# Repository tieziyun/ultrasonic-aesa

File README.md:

# Ultrasonic AESA panel

A 40 kHz in-air phased array, an acoustic "AESA". It has 64 transducers in an 8 × 8 grid, and each one can transmit or listen under FPGA control, element by element and ping by ping. Eight wideband MEMS microphones sit around the edge of the grid. Every element's raw waveform (amplitude and phase) is digitised and streamed to an ALINX AXU3EGB (Zynq UltraScale+ ZU3EG) board, which does the beamforming.

Uses: 3-D sonar imaging, gesture and hand tracking, Doppler motion sensing, and continuous-wave split mode, where some elements transmit while the rest listen.

**Status (2026-10-24):** the schematic is complete and passes ERC (0 violations). All parts are placed on the 4-layer board (DRC clean, every part with a 3D model); routing is next. Full requirements, decisions and part choices are in [DESIGN_BRIEF.md](DESIGN_BRIEF.md).

## Read the schematic

**[docs/schematics/aesa_schematic.pdf](docs/schematics/aesa_schematic.pdf)**: the whole schematic in one PDF, one A3 page per sheet, regenerated on every schematic change. Page 1 is a block diagram of how the signal flows; click a block to open its sheet, and "<< up to" at the top of each page to go back. The bookmarks follow the hierarchy.

| Page | Sheet | What it is |
|---|---|---|
| 1 | top | **Block diagram**: FPGA → TX drive → transceivers → receive amplifiers → ADCs → FPGA, plus mics and power |
| 2 | `headers` | The two 40-pin ribbon headers to the AXU3EGB, idle pulls and I²C pull-ups |
| 3 | group | The 10 clock buffers and which clock each one feeds |
| 4 | `clk_buf` ×10 | One clock fan-out buffer with 47 Ω series termination |
| 5 | group | TX drive: 16 TX groups and 4 enable buffers |
| 6 | `tx_group` ×16 | 74HCT595 shift register and two UCC27524 gate drivers: drives 4 elements |
| 7 | `en_buf` ×4 | TX-enable buffer for 8 gate drivers |
| 8 | group | The 64 transceiver channels as an 8 × 8 grid |
| 9 | `channel` ×64 | One transceiver: crossed-diode T/R switch, CUSP-TR80 element, limiter, OPA1678 gain stage, 40 kHz band-pass |
| 10 | group | The 16 ADCs, which channels each one digitises, and their I²C groups |
| 11 | `adc` ×16 | TLV320ADC5140, 4 channels at 192 kSPS, input divider, TDM output to the FPGA |
| 12 | group | The 8 microphones, paired on 4 data lines |
| 13 | `mic` ×8 | SPH0641LU4H-1 PDM microphone |
| 14 | `power` | Power 1: 12 V jack → eFuse → VIN, +5 V buck, VDRV 15 V boost (switchable), +3V3, 3V3_MIC, ground test points |
| 15 | `power_analog` | Power 2 (analog): ±6.5 V → low-noise ±5VA for the receivers, +3V3A for the ADCs; the power tree and a bring-up checklist with the expected voltage at every test point |

Each block that repeats is drawn once and reused, so a change to `channel` applies to all 64 channels. KiCad's own export of every instance (126 pages) is left in `build/aesa_schematic_full.pdf`.

## Key numbers

| | |
|---|---|
| Elements | 64 × Same Sky CUSP-TR80-15-2500-TH (40 kHz transceiver, Ø9.8 mm) + 8 × SPH0641LU4H-1 MEMS mics |
| TX drive | 0–15 V square wave per element, 16 serial data lines at 10 MHz, per-element per-sample control |
| RX chain | Gain ×22 (+27 dB) in the amplifier, ×6.7 (+16.5 dB) to the ADC pin after the input divider; 31–51 kHz pass band; 1 m echo 93 dB above the noise ([simulated](sim/reports/README.md)) |
| ADC | 16 × TI TLV320ADC5140, 24-bit, 192 kSPS per channel, all 64 channels sampled at once, TDM to the FPGA, I²C configuration |
| Power | One 12 V barrel jack (≥ 1.5 A); every rail has a test point, an isolation jumper and (except the analog LDOs) an LED |
| Board | One 4-layer board, 192 × 301 mm (JLC04161H-7628, ENIG): transducers on the front, all SMT parts on the back |
| FPGA link | Two 40-pin ribbons, 3.3 V LVCMOS, about 15 cm |

## Repository

| Path | Contents |
|---|---|
| [DESIGN_BRIEF.md](DESIGN_BRIEF.md) | Requirements, decisions with reasons and sources, parts, pinouts, open questions |
| `kicad/` | KiCad 10 project `aesa.kicad_pro`, the source of truth |
| `scripts/` | Generators: `build_cells.py` (every cell sheet except `channel`: ADC, TX, buffers, mic, headers, power), `gen_top.py` (block diagram, group sheets, references), `sch_annotate.py` (channel title and notes), `export_pdf.py` (PDFs), plus field and LCSC helpers |
| `skidl/` | Reference spec of each block in SKiDL (values, nets, LCSC numbers) |
| `sim/` | LTspice testbenches and models. `sim/run.py` exports the channel circuit from the KiCad schematic, runs every testbench and writes [sim/reports/](sim/reports/README.md) |
| `docs/schematics/` | The schematic PDF (one page per sheet, linked) |
| `docs/assembly/` | Assembly drawing (front and back with every reference), for building and repair |
| `docs/datasheets/` | A datasheet PDF for every part on the board, with an [index](docs/datasheets/README.md); kept in step with the BOM by `scripts/datasheets.py` |
| [CLAUDE.md](CLAUDE.md) | Working rules for the AI assistant on this project |

## Rebuild

Tools: KiCad 10.0 (per-user install) and LTspice 24. Run from the repository root in a Windows terminal:

```
set KPY=%LOCALAPPDATA%\Programs\KiCad\10.0\bin\python.exe
set KCLI=%LOCALAPPDATA%\Programs\KiCad\10.0\bin\kicad-cli.exe
%KPY% scripts\build_cells.py
%KPY% scripts\sch_annotate.py
%KPY% scripts\sch_lcsc.py kicad\adc.kicad_sch kicad\tx_group.kicad_sch kicad\en_buf.kicad_sch kicad\clk_buf.kicad_sch kicad\mic.kicad_sch kicad\headers.kicad_sch kicad\power.kicad_sch kicad\power_analog.kicad_sch
%KPY% scripts\gen_top.py
%KCLI% sch erc kicad\aesa.kicad_sch
%KPY% sim\run.py
```

The `channel` sheet is drawn by hand (with the KiCad MCP server) and is not regenerated; everything else is. `gen_top.py` ends by exporting the schematic PDF, and the git pre-commit hook (`.githooks/pre-commit`, enabled with `git config core.hooksPath .githooks`) refuses a commit that changes a sheet without the matching PDF.

Board (placement, 3D models, assembly drawing):

```
%KPY% scripts\make_3d.py
%KPY% scripts\place.py
%KPY% scripts\placement_check.py
%KCLI% pcb drc kicadesa.kicad_pcb
%KPY% scriptsssembly_pdf.py
```

BOM (needs internet: it queries JLCPCB for parts, stock and prices, and takes a few minutes):

```
%KPY% scripts\bom.py
%KPY% scripts\sch_lcsc.py --force kicad\channel.kicad_sch kicad\adc.kicad_sch kicad\tx_group.kicad_sch kicad\en_buf.kicad_sch kicad\clk_buf.kicad_sch kicad\mic.kicad_sch kicad\headers.kicad_sch kicad\power.kicad_sch kicad\power_analog.kicad_sch
%KPY% scripts\gen_top.py
```

`bom.py` writes the costed BOM `docs/bom.md`, the JLCPCB upload file `fab/bom_jlcpcb.csv` and `scripts/parts.json`, from which `sch_lcsc.py` fills every part's LCSC field.

## Next

1. Routing (power by hand first, then Freerouting), then fabrication outputs for JLCPCB.
2. Waveguide design and FPGA firmware (XDC constraints, ADC register setup, TX bit streaming).

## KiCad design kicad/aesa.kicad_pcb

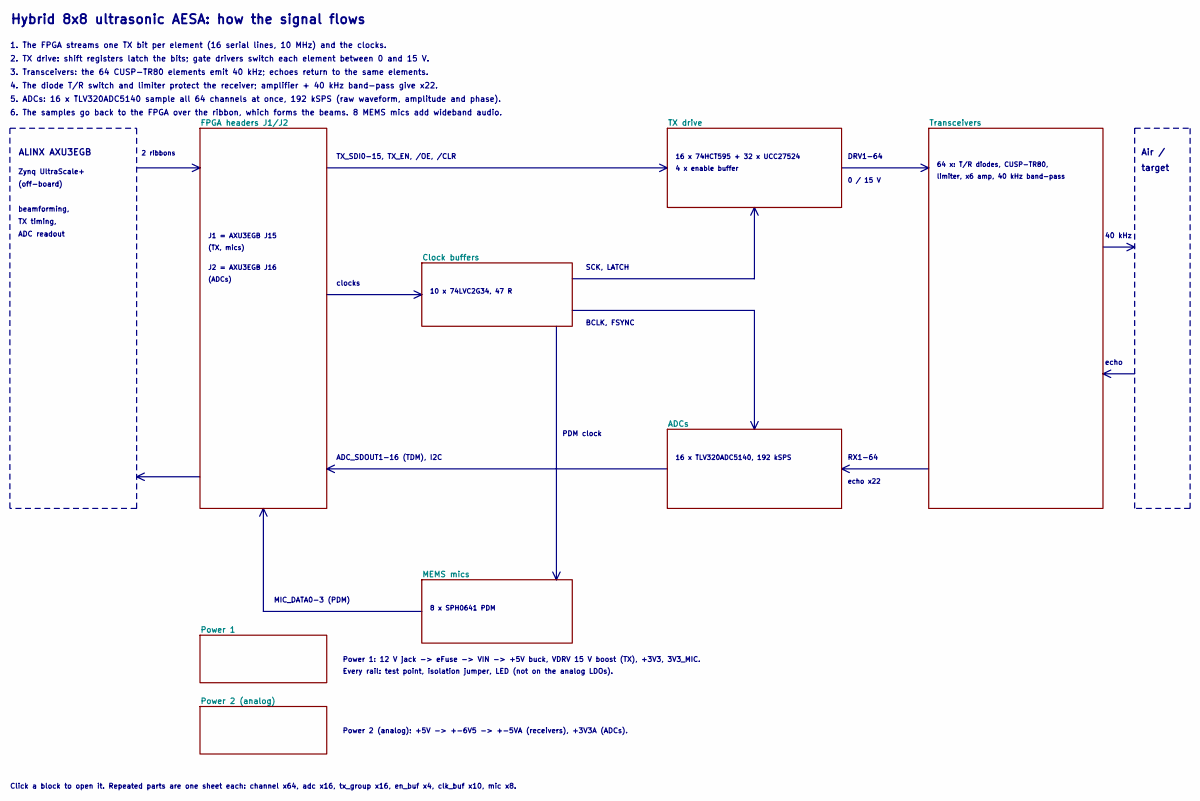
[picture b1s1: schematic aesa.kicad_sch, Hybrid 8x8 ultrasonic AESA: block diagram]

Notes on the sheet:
Hybrid 8x8 ultrasonic AESA: how the signal flows
1. The FPGA streams one TX bit per element (16 serial lines, 10 MHz) and the clocks.
2. TX drive: shift registers latch the bits; gate drivers switch each element between 0 and 15 V.
3. Transceivers: the 64 CUSP-TR80 elements emit 40 kHz; echoes return to the same elements.
4. The diode T/R switch and limiter protect the receiver; amplifier + 40 kHz band-pass give x22.
5. ADCs: 16 x TLV320ADC5140 sample all 64 channels at once, 192 kSPS (raw waveform, amplitude and phase).
6. The samples go back to the FPGA over the ribbon, which forms the beams. 8 MEMS mics add wideband audio.
ALINX AXU3EGB
Zynq UltraScale+
(off-board)
beamforming,
TX timing,
ADC readout
Air /
target
2 ribbons
TX_SDI0-15, TX_EN, /OE, /CLR
clocks
SCK, LATCH
BCLK, FSYNC
PDM clock
DRV1-64
0 / 15 V
40 kHz
echo
RX1-64
echo x22
ADC_SDOUT1-16 (TDM), I2C
MIC_DATA0-3 (PDM)
16 x 74HCT595 + 32 x UCC27524
4 x enable buffer
64 x: T/R diodes, CUSP-TR80,
limiter, x6 amp, 40 kHz band-pass
16 x TLV320ADC5140, 192 kSPS
10 x 74LVC2G34, 47 R
8 x SPH0641 PDM
J1 = AXU3EGB J15
(TX, mics)
J2 = AXU3EGB J16
(ADCs)

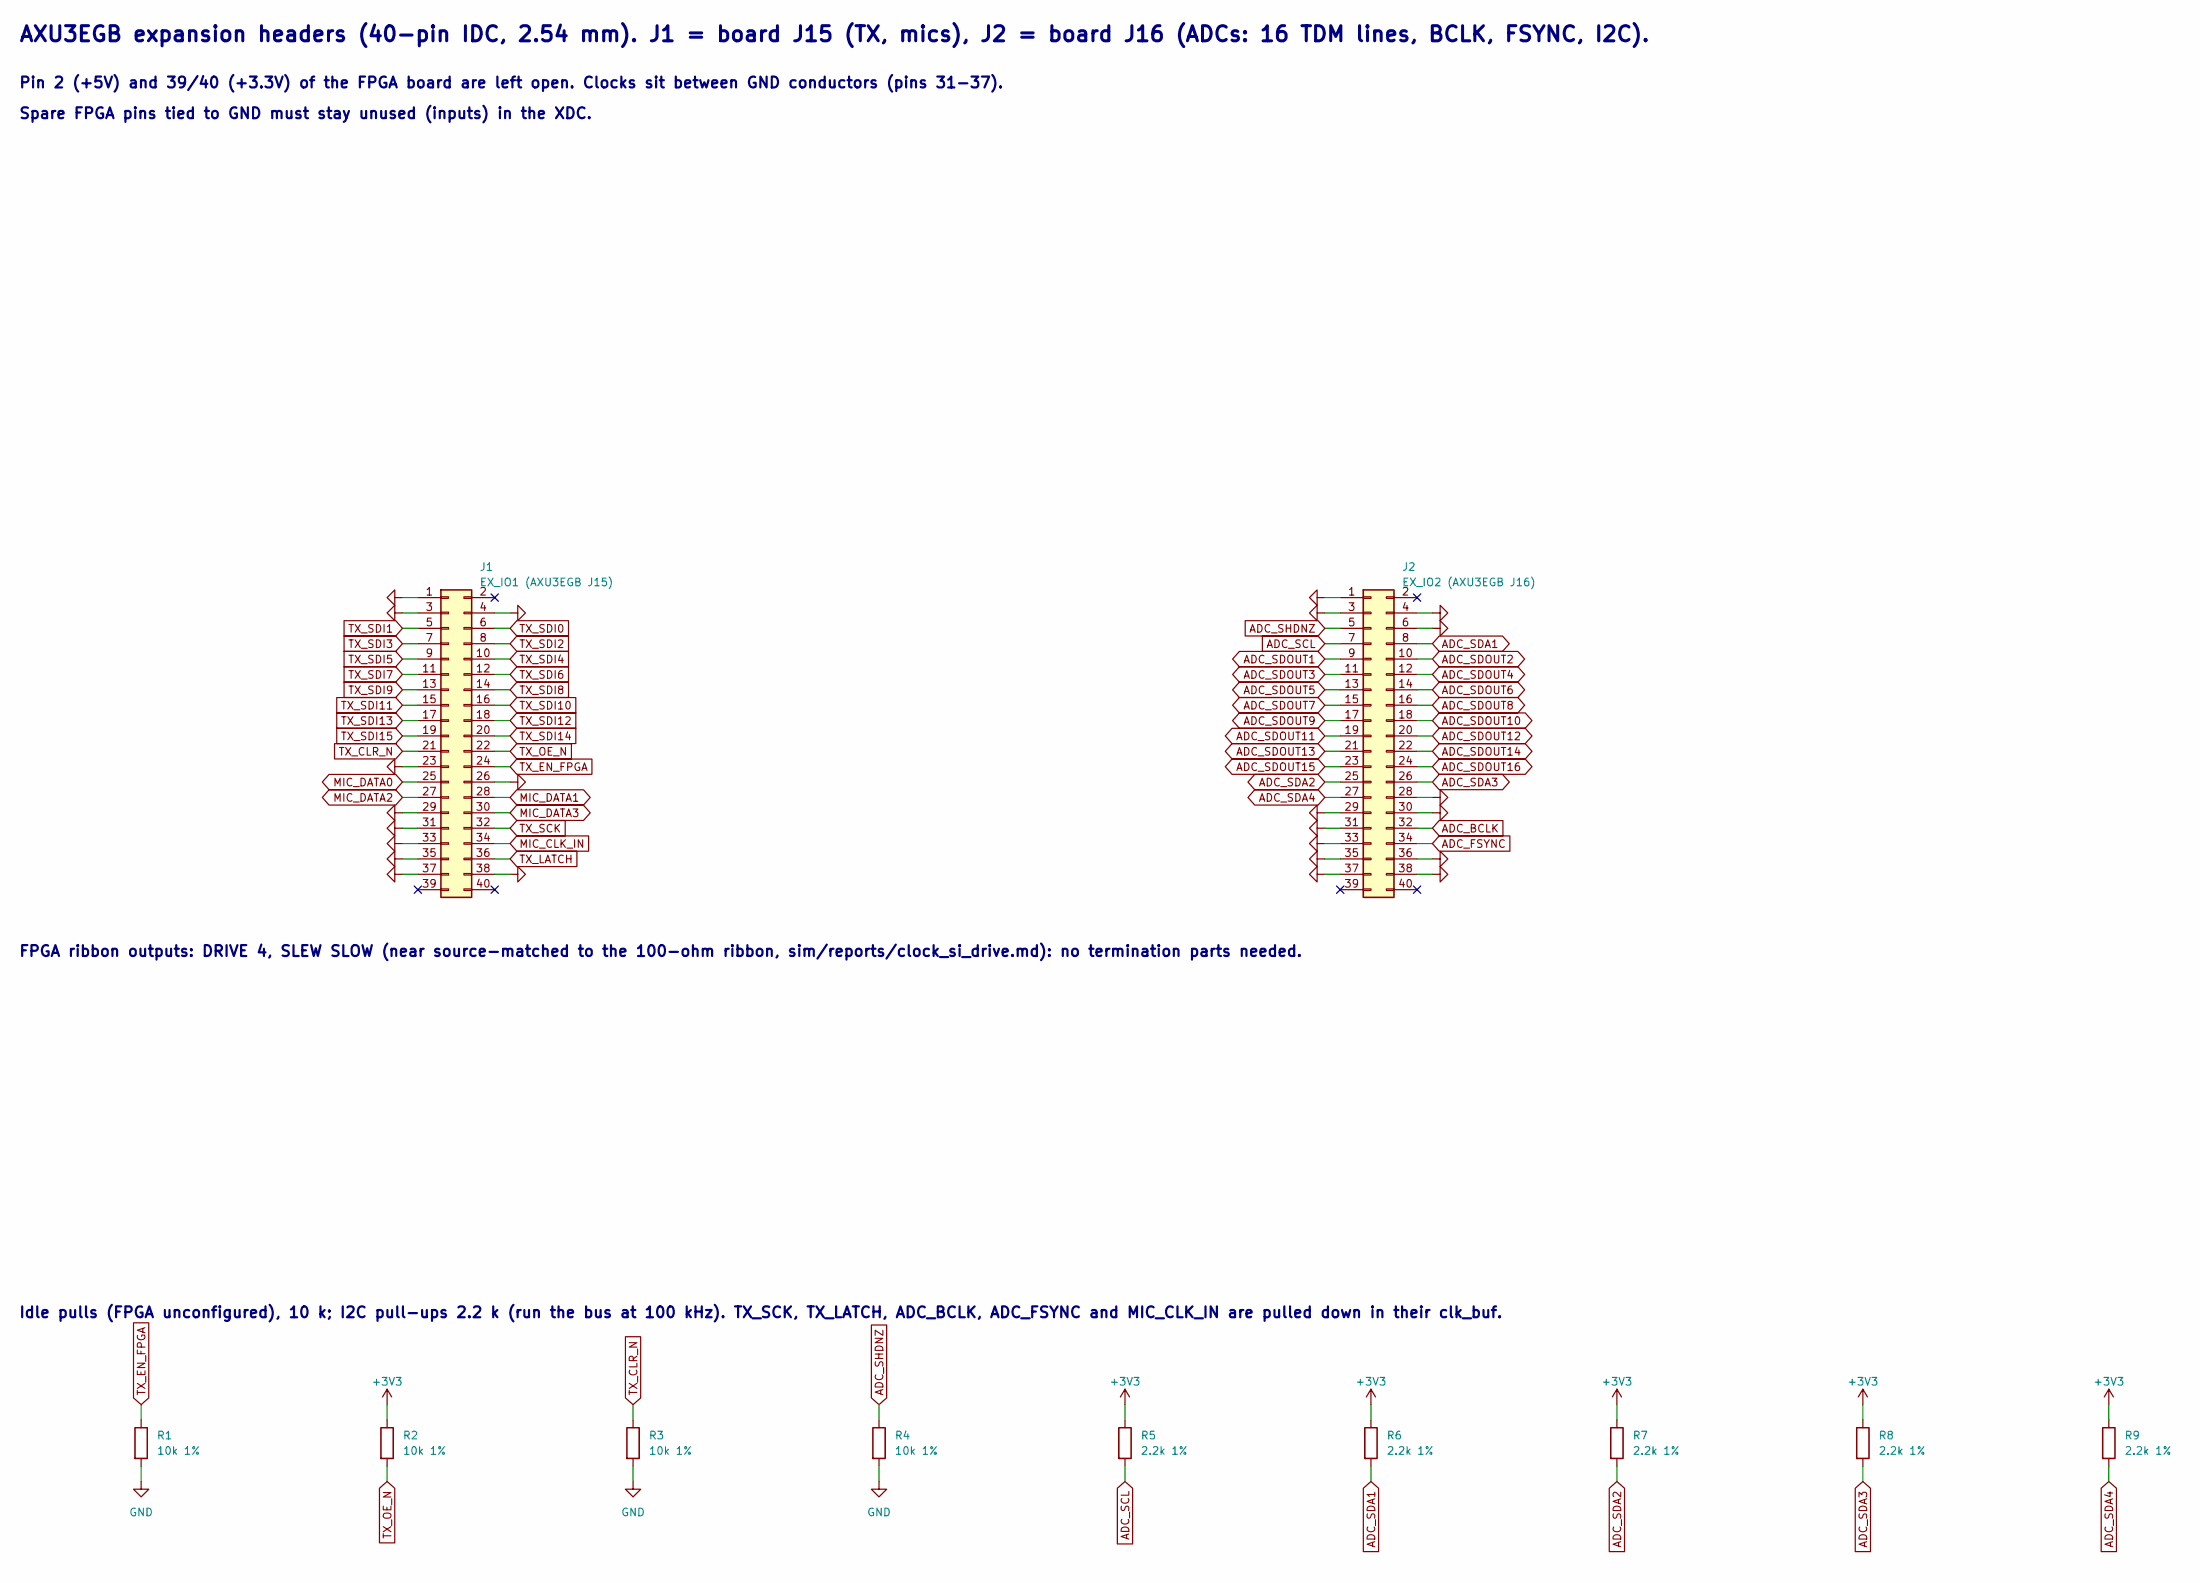
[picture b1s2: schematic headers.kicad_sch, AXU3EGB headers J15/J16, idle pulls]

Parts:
J1: EX_IO1 (AXU3EGB J15); IDC-Header_2x20_P2.54mm_Vertical; LCSC C19193815
J2: EX_IO2 (AXU3EGB J16); IDC-Header_2x20_P2.54mm_Vertical; LCSC C19193815
R1, R2, R3, R4: 10k 1%; R_0603_1608Metric; LCSC C25804
R5, R6, R7, R8, R9: 2.2k 1%; R_0603_1608Metric; LCSC C4190

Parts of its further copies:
J9901: EX_IO1 (AXU3EGB J15); IDC-Header_2x20_P2.54mm_Vertical; LCSC C19193815
J9902: EX_IO2 (AXU3EGB J16); IDC-Header_2x20_P2.54mm_Vertical; LCSC C19193815
R9901, R9902, R9903, R9904: 10k 1%; R_0603_1608Metric; LCSC C25804
R9905, R9906, R9907, R9908, R9909: 2.2k 1%; R_0603_1608Metric; LCSC C4190

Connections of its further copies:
+3V3: R9902.1, R9905.1, R9906.1, R9907.1, R9908.1, R9909.1; also elsewhere on the board
ADC_BCLK: J9902.32; also elsewhere on the board
ADC_FSYNC: J9902.34; also elsewhere on the board
ADC_SCL: J9902.7, R9905.2; also elsewhere on the board
ADC_SDA1: J9902.8, R9906.2; also elsewhere on the board
ADC_SDA2: J9902.25, R9907.2; also elsewhere on the board
ADC_SDA3: J9902.26, R9908.2; also elsewhere on the board
ADC_SDA4: J9902.27, R9909.2; also elsewhere on the board
ADC_SDOUT1: J9902.9; also elsewhere on the board
ADC_SDOUT2: J9902.10; also elsewhere on the board
ADC_SDOUT3: J9902.11; also elsewhere on the board
ADC_SDOUT4: J9902.12; also elsewhere on the board
ADC_SDOUT5: J9902.13; also elsewhere on the board
ADC_SDOUT6: J9902.14; also elsewhere on the board
ADC_SDOUT7: J9902.15; also elsewhere on the board
ADC_SDOUT8: J9902.16; also elsewhere on the board
ADC_SDOUT9: J9902.17; also elsewhere on the board
ADC_SDOUT10: J9902.18; also elsewhere on the board
ADC_SDOUT11: J9902.19; also elsewhere on the board
ADC_SDOUT12: J9902.20; also elsewhere on the board
ADC_SDOUT13: J9902.21; also elsewhere on the board
ADC_SDOUT14: J9902.22; also elsewhere on the board
ADC_SDOUT15: J9902.23; also elsewhere on the board
ADC_SDOUT16: J9902.24; also elsewhere on the board
ADC_SHDNZ: J9902.5, R9904.1; also elsewhere on the board
GND: J9901.1, J9901.3, J9901.4, J9901.23, J9901.26, J9901.29, J9901.31, J9901.33, J9901.35, J9901.37, J9901.38, J9902.1, J9902.3, J9902.4, J9902.6, J9902.28, J9902.29, J9902.30, J9902.31, J9902.33, J9902.35, J9902.36, J9902.37, J9902.38, R9901.2, R9903.2, R9904.2; also elsewhere on the board
MIC_CLK_IN: J9901.34; also elsewhere on the board
MIC_DATA0: J9901.25; also elsewhere on the board
MIC_DATA1: J9901.28; also elsewhere on the board
MIC_DATA2: J9901.27; also elsewhere on the board
MIC_DATA3: J9901.30; also elsewhere on the board
TX_CLR_N: J9901.21, R9903.1; also elsewhere on the board
TX_EN_FPGA: J9901.24, R9901.1; also elsewhere on the board
TX_LATCH: J9901.36; also elsewhere on the board
TX_OE_N: J9901.22, R9902.2; also elsewhere on the board
TX_SCK: J9901.32; also elsewhere on the board
TX_SDI0: J9901.6; also elsewhere on the board
TX_SDI1: J9901.5; also elsewhere on the board
TX_SDI2: J9901.8; also elsewhere on the board
TX_SDI3: J9901.7; also elsewhere on the board
TX_SDI4: J9901.10; also elsewhere on the board
TX_SDI5: J9901.9; also elsewhere on the board
TX_SDI6: J9901.12; also elsewhere on the board
TX_SDI7: J9901.11; also elsewhere on the board
TX_SDI8: J9901.14; also elsewhere on the board
TX_SDI9: J9901.13; also elsewhere on the board
TX_SDI10: J9901.16; also elsewhere on the board
TX_SDI11: J9901.15; also elsewhere on the board
TX_SDI12: J9901.18; also elsewhere on the board
TX_SDI13: J9901.17; also elsewhere on the board
TX_SDI14: J9901.20; also elsewhere on the board
TX_SDI15: J9901.19; also elsewhere on the board

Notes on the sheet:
Idle pulls (FPGA unconfigured), 10 k; I2C pull-ups 2.2 k (run the bus at 100 kHz). TX_SCK, TX_LATCH, ADC_BCLK, ADC_FSYNC and MIC_CLK_IN are pulled down in their clk_buf.
Pin 2 (+5V) and 39/40 (+3.3V) of the FPGA board are left open. Clocks sit between GND conductors (pins 31-37).
Spare FPGA pins tied to GND must stay unused (inputs) in the XDC.
AXU3EGB expansion headers (40-pin IDC, 2.54 mm). J1 = board J15 (TX, mics), J2 = board J16 (ADCs: 16 TDM lines, BCLK, FSYNC, I2C).
FPGA ribbon outputs: DRIVE 4, SLEW SLOW (near source-matched to the 100-ohm ribbon, sim/reports/clock_si_drive.md): no termination parts needed.

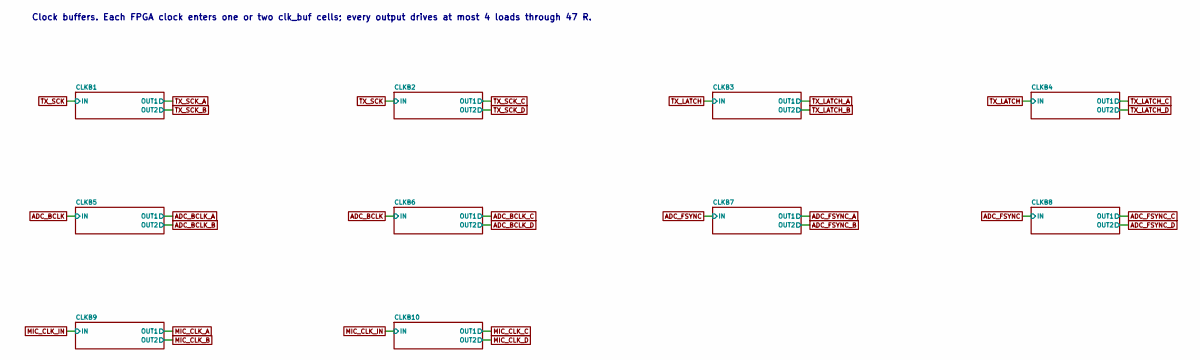
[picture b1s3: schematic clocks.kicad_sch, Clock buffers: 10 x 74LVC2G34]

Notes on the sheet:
Clock buffers. Each FPGA clock enters one or two clk_buf cells; every output drives at most 4 loads through 47 R.

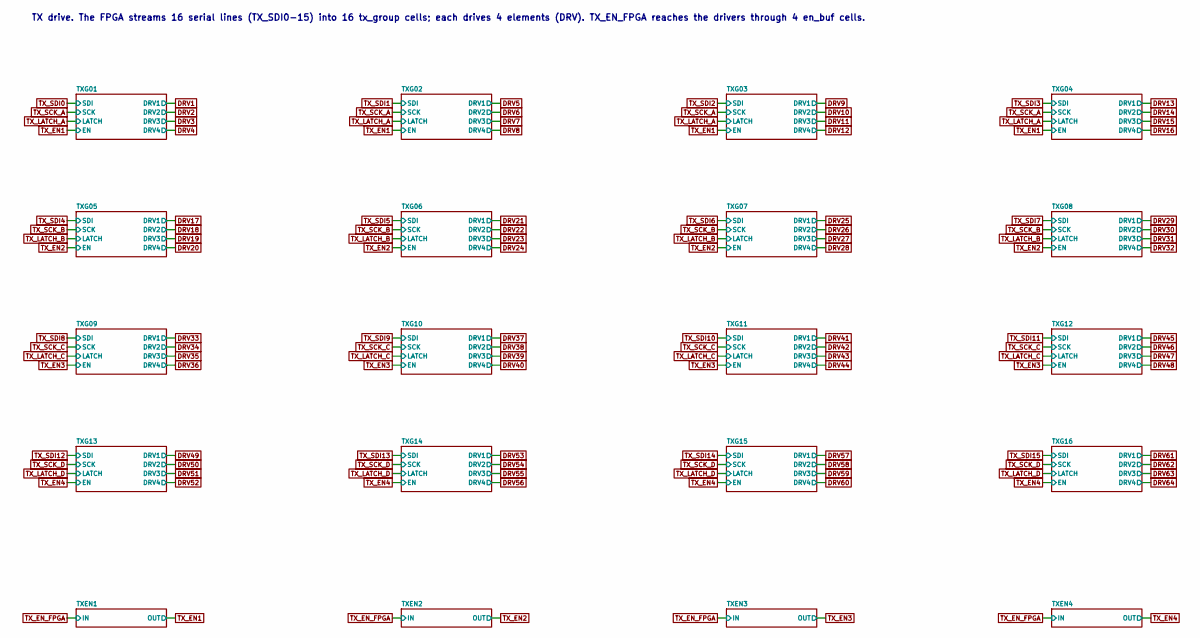
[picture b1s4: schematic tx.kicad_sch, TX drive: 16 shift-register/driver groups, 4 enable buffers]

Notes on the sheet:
TX drive. The FPGA streams 16 serial lines (TX_SDI0-15) into 16 tx_group cells; each drives 4 elements (DRV). TX_EN_FPGA reaches the drivers through 4 en_buf cells.

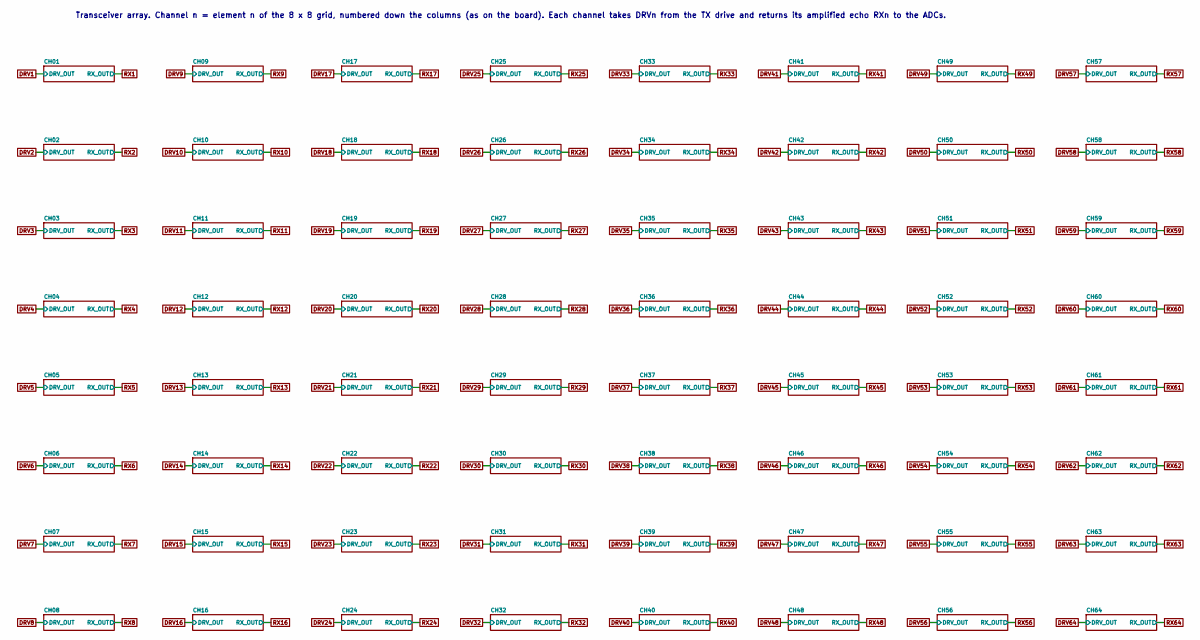
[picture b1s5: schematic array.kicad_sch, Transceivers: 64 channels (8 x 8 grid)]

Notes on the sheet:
Transceiver array. Channel n = element n of the 8 x 8 grid, numbered down the columns (as on the board). Each channel takes DRVn from the TX drive and returns its amplified echo RXn to the ADCs.

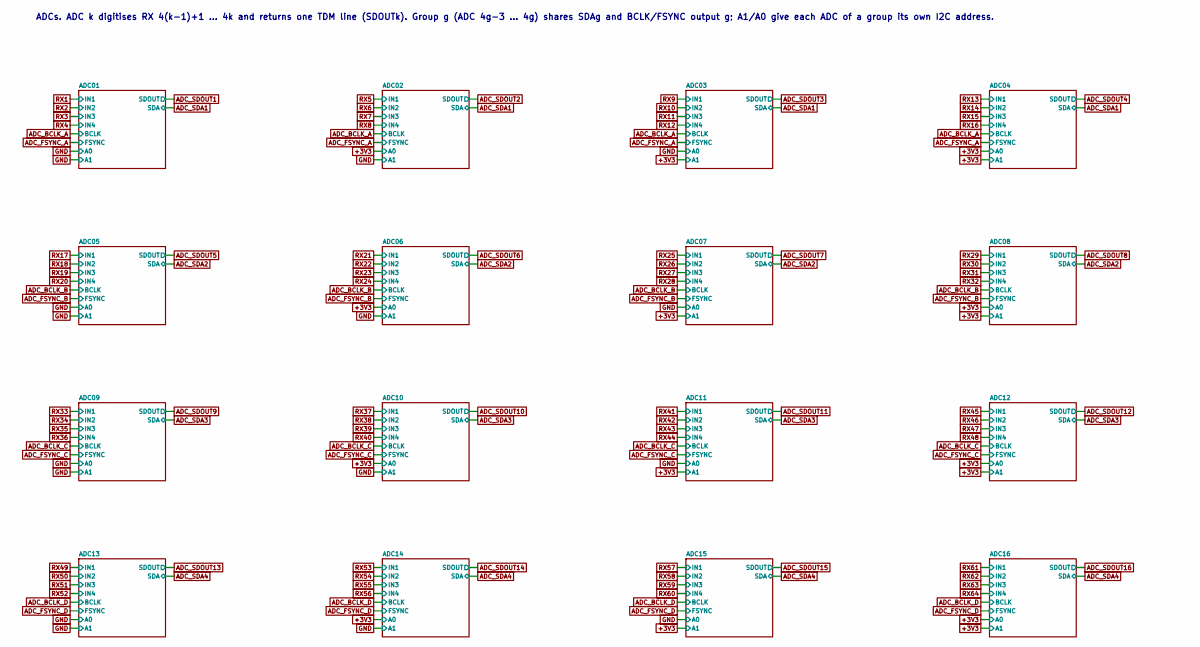
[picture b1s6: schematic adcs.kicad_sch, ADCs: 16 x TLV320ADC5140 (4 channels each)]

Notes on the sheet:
ADCs. ADC k digitises RX 4(k-1)+1 ... 4k and returns one TDM line (SDOUTk). Group g (ADC 4g-3 ... 4g) shares SDAg and BCLK/FSYNC output g; A1/A0 give each ADC of a group its own I2C address.

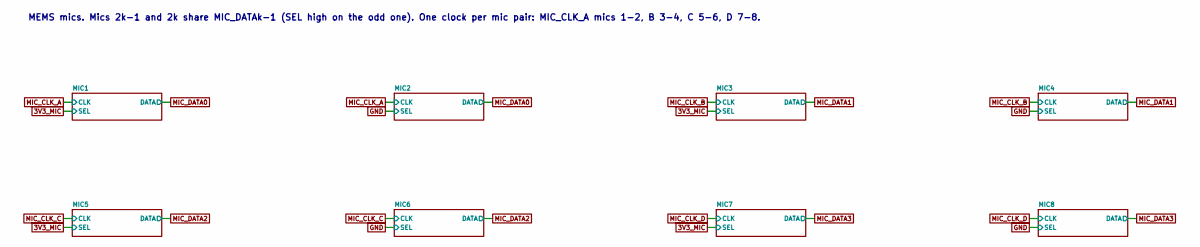
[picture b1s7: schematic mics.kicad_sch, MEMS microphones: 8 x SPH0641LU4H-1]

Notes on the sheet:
MEMS mics. Mics 2k-1 and 2k share MIC_DATAk-1 (SEL high on the odd one). One clock per mic pair: MIC_CLK_A mics 1-2, B 3-4, C 5-6, D 7-8.

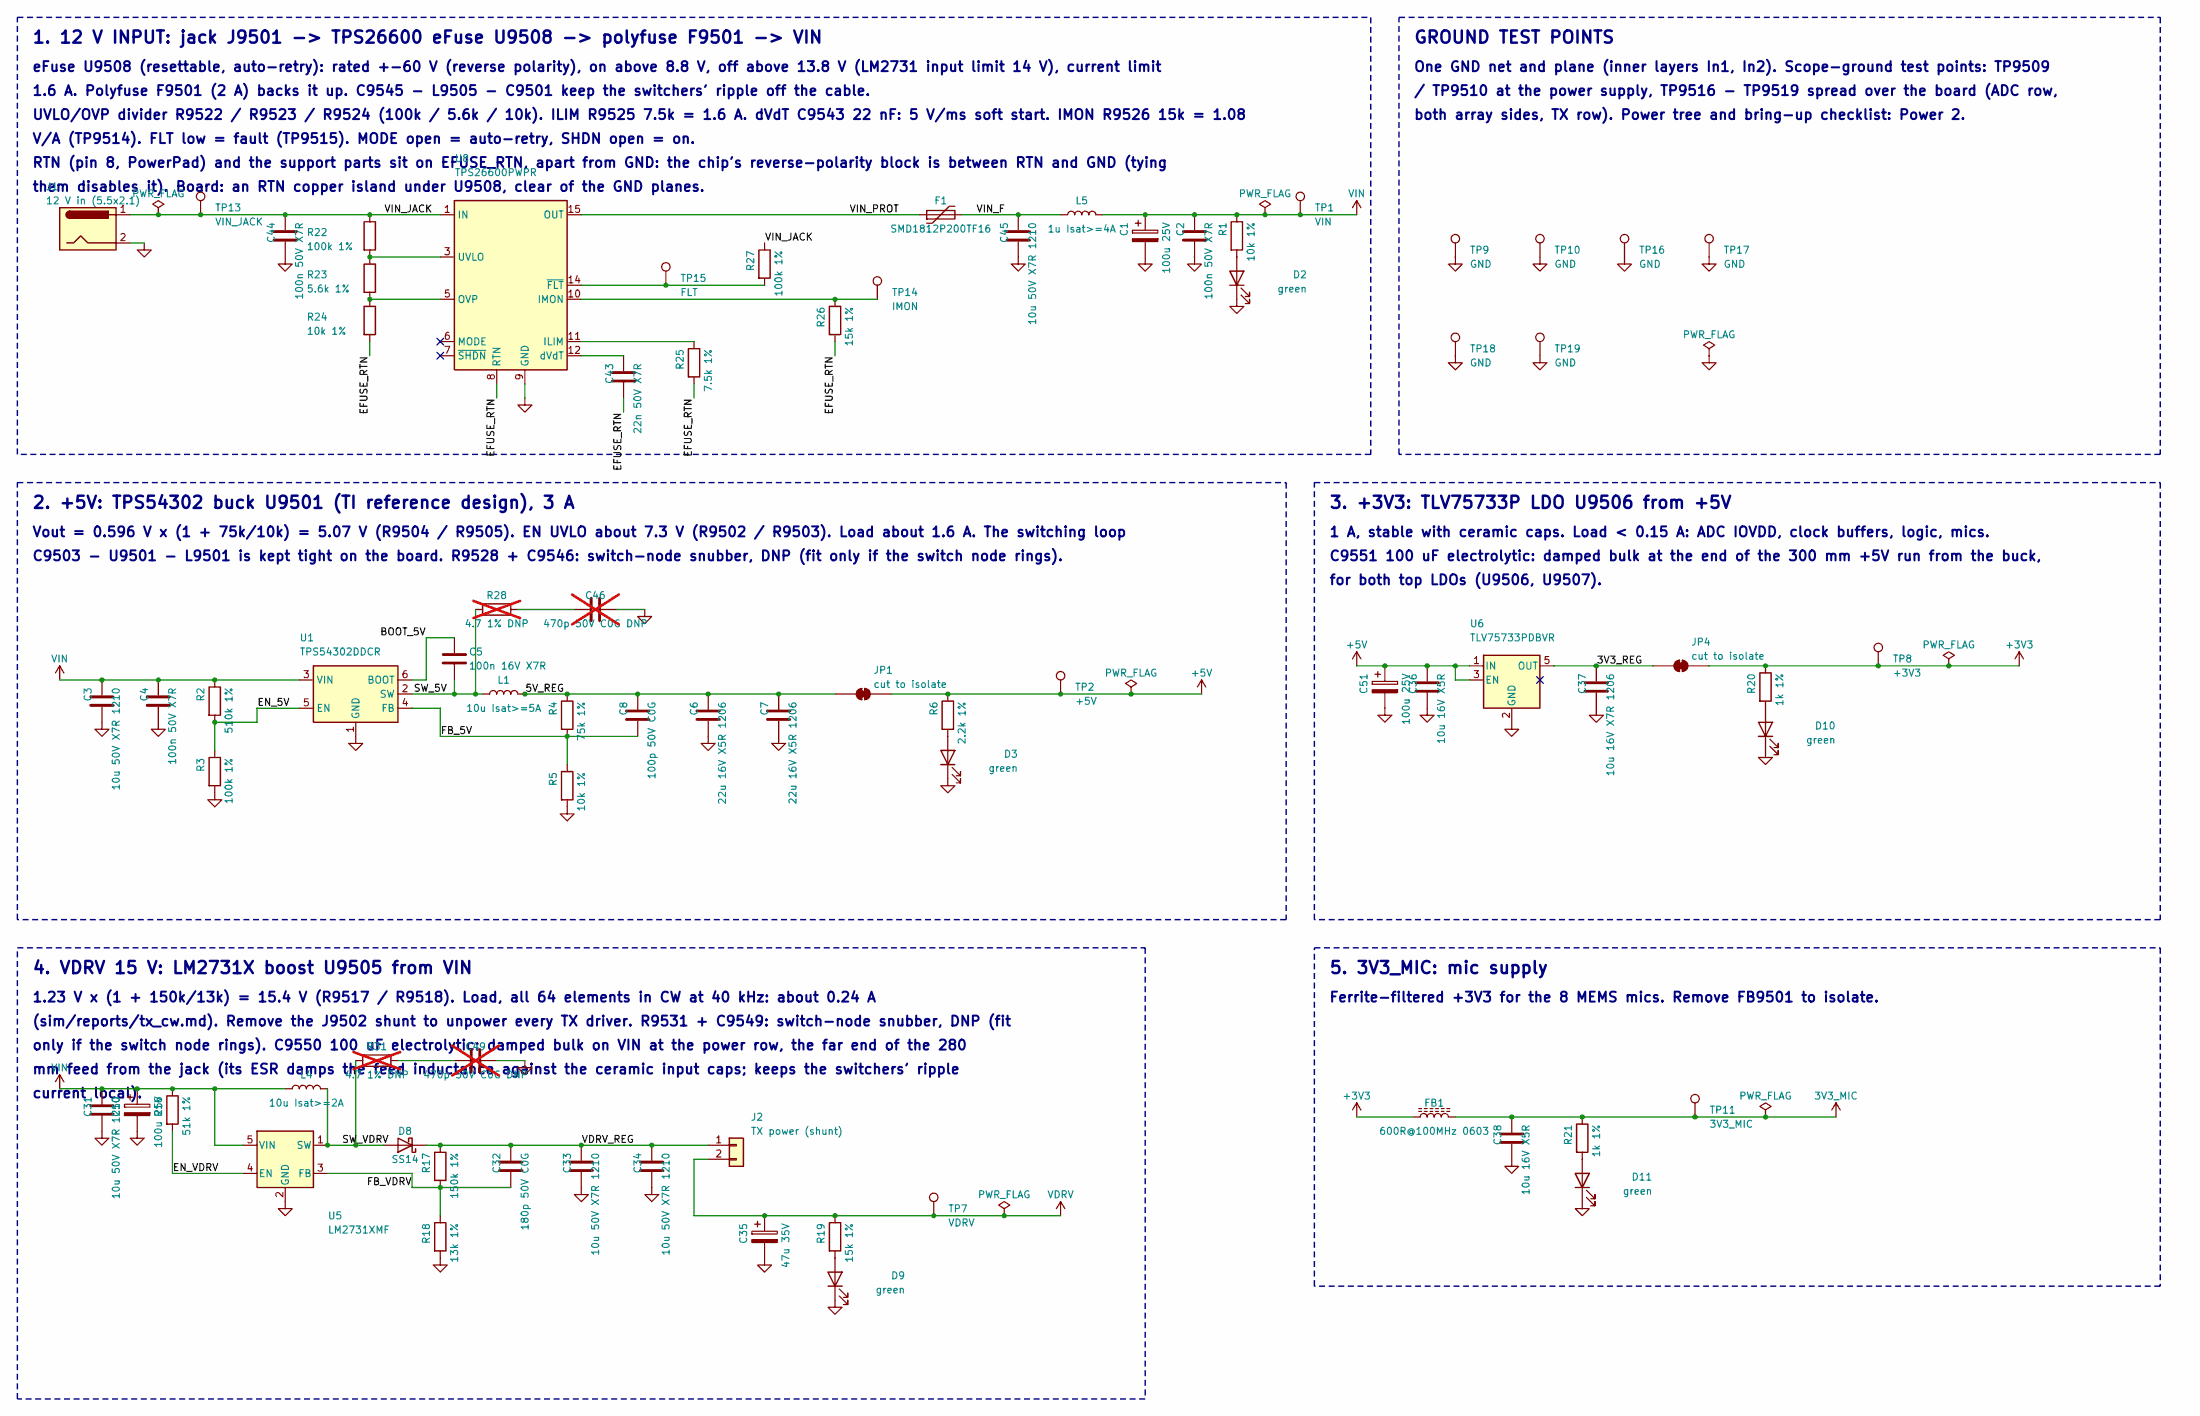
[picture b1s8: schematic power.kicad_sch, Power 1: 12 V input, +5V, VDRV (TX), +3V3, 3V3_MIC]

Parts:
C1, C50, C51: 100u 25V; CP_Elec_8x10; LCSC C294509
C2, C4, C44: 100n 50V X7R; C_0603_1608Metric; LCSC C14663
C3, C31, C33, C34, C45: 10u 50V X7R 1210; C_1210_3225Metric; LCSC C525507
C5: 100n 16V X7R; C_0603_1608Metric; LCSC C14663
C6, C7: 22u 16V X5R 1206; C_1206_3216Metric; LCSC C12891
C8: 100p 50V C0G; C_0603_1608Metric; LCSC C14858
C32: 180p 50V C0G; C_0603_1608Metric; LCSC C376771
C35: 47u 35V; CP_Elec_6.3x7.7; LCSC C970679
C36, C38: 10u 16V X5R; C_0805_2012Metric; LCSC C15850
C37: 10u 16V X7R 1206; C_1206_3216Metric; LCSC C380363
C43: 22n 50V X7R; C_0603_1608Metric; LCSC C21122
C46, C49: 470p 50V C0G DNP; C_0603_1608Metric; LCSC C376788 (DNP); not fitted
D2, D3, D9, D10, D11: green; LED_0603_1608Metric; LCSC C12624
D8: SS14; D_SMA; LCSC C2480
F1: SMD1812P200TF16; Fuse_1812_4532Metric; LCSC C20812
FB1: 600R@100MHz 0603; L_0603_1608Metric; LCSC C1002
J1: 12 V in (5.5x2.1); BarrelJack_CUI_PJ-063AH_Horizontal; LCSC C22434582
J2: TX power (shunt); PinHeader_1x02_P2.54mm_Vertical; LCSC C492401
JP1, JP4: cut to isolate; SolderJumper-2_P1.3mm_Bridged_RoundedPad1.0x1.5mm; LCSC none (copper)
L1: 10u Isat>=5A; L_Bourns_SRN8040TA; LCSC C2044906
L4: 10u Isat>=2A; L_Sunlord_SWPA6045S; LCSC C79272
L5: 1u Isat>=4A; L_Sunlord_SWPA4030S; LCSC C42193
R1, R5, R24: 10k 1%; R_0603_1608Metric; LCSC C25804
R2: 510k 1%; R_0603_1608Metric; LCSC C23192
R3, R22, R27: 100k 1%; R_0603_1608Metric; LCSC C25803
R4: 75k 1%; R_0603_1608Metric; LCSC C23242
R6: 2.2k 1%; R_0603_1608Metric; LCSC C4190
R16: 51k 1%; R_0603_1608Metric; LCSC C23196
R17: 150k 1%; R_0603_1608Metric; LCSC C22807
R18: 13k 1%; R_0603_1608Metric; LCSC C22797
R19, R26: 15k 1%; R_0603_1608Metric; LCSC C22809
R20, R21: 1k 1%; R_0603_1608Metric; LCSC C21190
R23: 5.6k 1%; R_0603_1608Metric; LCSC C23189
R25: 7.5k 1%; R_0603_1608Metric; LCSC C23234
R28, R31: 4.7 1% DNP; R_0603_1608Metric; LCSC C23164 (DNP); not fitted
TP1: VIN; TestPoint_Pad_D1.5mm; LCSC none (copper)
TP2: +5V; TestPoint_Pad_D1.5mm; LCSC none (copper)
TP7: VDRV; TestPoint_Pad_D1.5mm; LCSC none (copper)
TP8: +3V3; TestPoint_Pad_D1.5mm; LCSC none (copper)
TP9, TP10, TP16, TP17, TP18, TP19: GND; TestPoint_Pad_D1.5mm; LCSC none (copper)
TP11: 3V3_MIC; TestPoint_Pad_D1.5mm; LCSC none (copper)
TP13: VIN_JACK; TestPoint_Pad_D1.5mm; LCSC none (copper)
TP14: IMON; TestPoint_Pad_D1.5mm; LCSC none (copper)
TP15: FLT; TestPoint_Pad_D1.5mm; LCSC none (copper)
U1: TPS54302DDCR; SOT-23-6; LCSC C311983
U5: LM2731XMF; SOT-23-5; LCSC C485804
U6: TLV75733PDBVR; SOT-23-5; LCSC C485517
U8: TPS26600PWPR; HTSSOP-16-1EP_4.4x5mm_P0.65mm_EP3.4x5mm_Mask2.66x2.46mm_The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; LCSC C544399

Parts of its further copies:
C9501, C9550, C9551: 100u 25V; CP_Elec_8x10; LCSC C294509
C9502, C9504, C9544: 100n 50V X7R; C_0603_1608Metric; LCSC C14663
C9503, C9531, C9533, C9534, C9545: 10u 50V X7R 1210; C_1210_3225Metric; LCSC C525507
C9505: 100n 16V X7R; C_0603_1608Metric; LCSC C14663
C9506, C9507: 22u 16V X5R 1206; C_1206_3216Metric; LCSC C12891
C9508: 100p 50V C0G; C_0603_1608Metric; LCSC C14858
C9532: 180p 50V C0G; C_0603_1608Metric; LCSC C376771
C9535: 47u 35V; CP_Elec_6.3x7.7; LCSC C970679
C9536, C9538: 10u 16V X5R; C_0805_2012Metric; LCSC C15850
C9537: 10u 16V X7R 1206; C_1206_3216Metric; LCSC C380363
C9543: 22n 50V X7R; C_0603_1608Metric; LCSC C21122
C9546, C9549: 470p 50V C0G DNP; C_0603_1608Metric; LCSC C376788 (DNP); not fitted
D9502, D9503, D9509, D9510, D9511: green; LED_0603_1608Metric; LCSC C12624
D9508: SS14; D_SMA; LCSC C2480
F9501: SMD1812P200TF16; Fuse_1812_4532Metric; LCSC C20812
FB9501: 600R@100MHz 0603; L_0603_1608Metric; LCSC C1002
J9501: 12 V in (5.5x2.1); BarrelJack_CUI_PJ-063AH_Horizontal; LCSC C22434582
J9502: TX power (shunt); PinHeader_1x02_P2.54mm_Vertical; LCSC C492401
JP9501, JP9504: cut to isolate; SolderJumper-2_P1.3mm_Bridged_RoundedPad1.0x1.5mm; LCSC none (copper)
L9501: 10u Isat>=5A; L_Bourns_SRN8040TA; LCSC C2044906
L9504: 10u Isat>=2A; L_Sunlord_SWPA6045S; LCSC C79272
L9505: 1u Isat>=4A; L_Sunlord_SWPA4030S; LCSC C42193
R9501, R9505, R9524: 10k 1%; R_0603_1608Metric; LCSC C25804
R9502: 510k 1%; R_0603_1608Metric; LCSC C23192
R9503, R9522, R9527: 100k 1%; R_0603_1608Metric; LCSC C25803
R9504: 75k 1%; R_0603_1608Metric; LCSC C23242
R9506: 2.2k 1%; R_0603_1608Metric; LCSC C4190
R9516: 51k 1%; R_0603_1608Metric; LCSC C23196
R9517: 150k 1%; R_0603_1608Metric; LCSC C22807
R9518: 13k 1%; R_0603_1608Metric; LCSC C22797
R9519, R9526: 15k 1%; R_0603_1608Metric; LCSC C22809
R9520, R9521: 1k 1%; R_0603_1608Metric; LCSC C21190
R9523: 5.6k 1%; R_0603_1608Metric; LCSC C23189
R9525: 7.5k 1%; R_0603_1608Metric; LCSC C23234
R9528, R9531: 4.7 1% DNP; R_0603_1608Metric; LCSC C23164 (DNP); not fitted
TP9501: VIN; TestPoint_Pad_D1.5mm; LCSC none (copper)
TP9502: +5V; TestPoint_Pad_D1.5mm; LCSC none (copper)
TP9507: VDRV; TestPoint_Pad_D1.5mm; LCSC none (copper)
TP9508: +3V3; TestPoint_Pad_D1.5mm; LCSC none (copper)
TP9509, TP9510, TP9516, TP9517, TP9518, TP9519: GND; TestPoint_Pad_D1.5mm; LCSC none (copper)
TP9511: 3V3_MIC; TestPoint_Pad_D1.5mm; LCSC none (copper)
TP9513: VIN_JACK; TestPoint_Pad_D1.5mm; LCSC none (copper)
TP9514: IMON; TestPoint_Pad_D1.5mm; LCSC none (copper)
TP9515: FLT; TestPoint_Pad_D1.5mm; LCSC none (copper)
U9501: TPS54302DDCR; SOT-23-6; LCSC C311983
U9505: LM2731XMF; SOT-23-5; LCSC C485804
U9506: TLV75733PDBVR; SOT-23-5; LCSC C485517
U9508: TPS26600PWPR; HTSSOP-16-1EP_4.4x5mm_P0.65mm_EP3.4x5mm_Mask2.66x2.46mm_The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; LCSC C544399

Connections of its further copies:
3V3_MIC: C9538.1, FB9501.2, R9521.1, TP9511.1; also elsewhere on the board
+3V3: FB9501.1, JP9504.2 (B), R9520.1, TP9508.1; also elsewhere on the board
+5V: C9536.1, C9551.1, JP9501.2 (B), R9506.1, TP9502.1, U9506.1 (IN), U9506.3 (EN); also elsewhere on the board
/Power 1/3V3_REG: C9537.1, JP9504.1 (A), U9506.5 (OUT)
/Power 1/5V_REG: C9506.1, C9507.1, C9508.1, JP9501.1 (A), L9501.2, R9504.1
/Power 1/BOOT_5V: C9505.1, U9501.6 (BOOT)
/Power 1/EFUSE_RTN: C9543.2, R9524.2, R9525.2, R9526.2, U9508.8 (RTN), U9508.17 (RTN)
/Power 1/EN_5V: R9502.2, R9503.1, U9501.5 (EN)
/Power 1/EN_VDRV: R9516.2, U9505.4 (EN)
/Power 1/FB_5V: C9508.2, R9504.2, R9505.1, U9501.4 (FB)
/Power 1/FB_VDRV: C9532.2, R9517.2, R9518.1, U9505.3 (FB)
/Power 1/SW_5V: C9505.2, L9501.1, R9528.1, U9501.2 (SW)
/Power 1/SW_VDRV: D9508.2 (A), L9504.2, R9531.1, U9505.1 (SW)
/Power 1/VDRV_REG: C9532.1, C9533.1, C9534.1, D9508.1 (K), J9502.1, R9517.1
/Power 1/VIN_F: C9545.1, F9501.2, L9505.1
/Power 1/VIN_JACK: C9544.1, J9501.1, R9522.1, R9527.1, TP9513.1, U9508.1 (IN), U9508.2 (IN)
/Power 1/VIN_PROT: F9501.1, U9508.15 (OUT), U9508.16 (OUT)
GND: C9501.2, C9502.2, C9503.2, C9504.2, C9506.2, C9507.2, C9531.2, C9533.2, C9534.2, C9535.2, C9536.2, C9537.2, C9538.2, C9544.2, C9545.2, C9546.2, C9549.2, C9550.2, C9551.2, D9502.1 (K), D9503.1 (K), D9509.1 (K), D9510.1 (K), D9511.1 (K), J9501.2, R9503.2, R9505.2, R9518.2, TP9509.1, TP9510.1, TP9516.1, TP9517.1, TP9518.1, TP9519.1, U9501.1 (GND), U9505.2 (GND), U9506.2 (GND), U9508.9 (GND); also elsewhere on the board
unnamed: C9546.1, R9528.2
unnamed: C9549.1, R9531.2
unnamed: D9502.2 (A), R9501.2
unnamed: D9503.2 (A), R9506.2
unnamed: D9509.2 (A), R9519.2
unnamed: D9510.2 (A), R9520.2
unnamed: D9511.2 (A), R9521.2
unnamed: R9525.1, U9508.11 (ILIM)
unnamed: R9526.1, TP9514.1, U9508.10 (IMON)
unnamed: R9523.2, R9524.1, U9508.5 (OVP)
unnamed: R9522.2, R9523.1, U9508.3 (UVLO)
unnamed: C9543.1, U9508.12 (dVdT)
unnamed: R9527.2, TP9515.1, U9508.14 (~FLT)
VDRV: C9535.1, J9502.2, R9519.1, TP9507.1; also elsewhere on the board
VIN: C9501.1, C9502.1, C9503.1, C9504.1, C9531.1, C9550.1, L9504.1, L9505.2, R9501.1, R9502.1, R9516.1, TP9501.1, U9501.3 (VIN), U9505.5 (VIN)

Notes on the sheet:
RTN (pin 8, PowerPad) and the support parts sit on EFUSE_RTN, apart from GND: the chip's reverse-polarity block is between RTN and GND (tying
1.23 V x (1 + 150k/13k) = 15.4 V (R9517 / R9518). Load, all 64 elements in CW at 40 kHz: about 0.24 A
One GND net and plane (inner layers In1, In2). Scope-ground test points: TP9509
(sim/reports/tx_cw.md). Remove the J9502 shunt to unpower every TX driver. R9531 + C9549: switch-node snubber, DNP (fit
for both top LDOs (U9506, U9507).
V/A (TP9514). FLT low = fault (TP9515). MODE open = auto-retry, SHDN open = on.
/ TP9510 at the power supply, TP9516 - TP9519 spread over the board (ADC row,
4. VDRV 15 V: LM2731X boost U9505 from VIN
both array sides, TX row). Power tree and bring-up checklist: Power 2.
current local).
them disables it). Board: an RTN copper island under U9508, clear of the GND planes.
only if the switch node rings). C9550 100 uF electrolytic: damped bulk on VIN at the power row, the far end of the 280
1 A, stable with ceramic caps. Load < 0.15 A: ADC IOVDD, clock buffers, logic, mics.
C9551 100 uF electrolytic: damped bulk at the end of the 300 mm +5V run from the buck,
eFuse U9508 (resettable, auto-retry): rated +-60 V (reverse polarity), on above 8.8 V, off above 13.8 V (LM2731 input limit 14 V), current limit
1.6 A. Polyfuse F9501 (2 A) backs it up. C9545 - L9505 - C9501 keep the switchers' ripple off the cable.
UVLO/OVP divider R9522 / R9523 / R9524 (100k / 5.6k / 10k). ILIM R9525 7.5k = 1.6 A. dVdT C9543 22 nF: 5 V/ms soft start. IMON R9526 15k = 1.08
2. +5V: TPS54302 buck U9501 (TI reference design), 3 A
1. 12 V INPUT: jack J9501 -> TPS26600 eFuse U9508 -> polyfuse F9501 -> VIN
mm feed from the jack (its ESR damps the feed inductance against the ceramic input caps; keeps the switchers' ripple
3. +3V3: TLV75733P LDO U9506 from +5V
Ferrite-filtered +3V3 for the 8 MEMS mics. Remove FB9501 to isolate.
GROUND TEST POINTS
C9503 - U9501 - L9501 is kept tight on the board. R9528 + C9546: switch-node snubber, DNP (fit only if the switch node rings).
5. 3V3_MIC: mic supply
Vout = 0.596 V x (1 + 75k/10k) = 5.07 V (R9504 / R9505). EN UVLO about 7.3 V (R9502 / R9503). Load about 1.6 A. The switching loop
